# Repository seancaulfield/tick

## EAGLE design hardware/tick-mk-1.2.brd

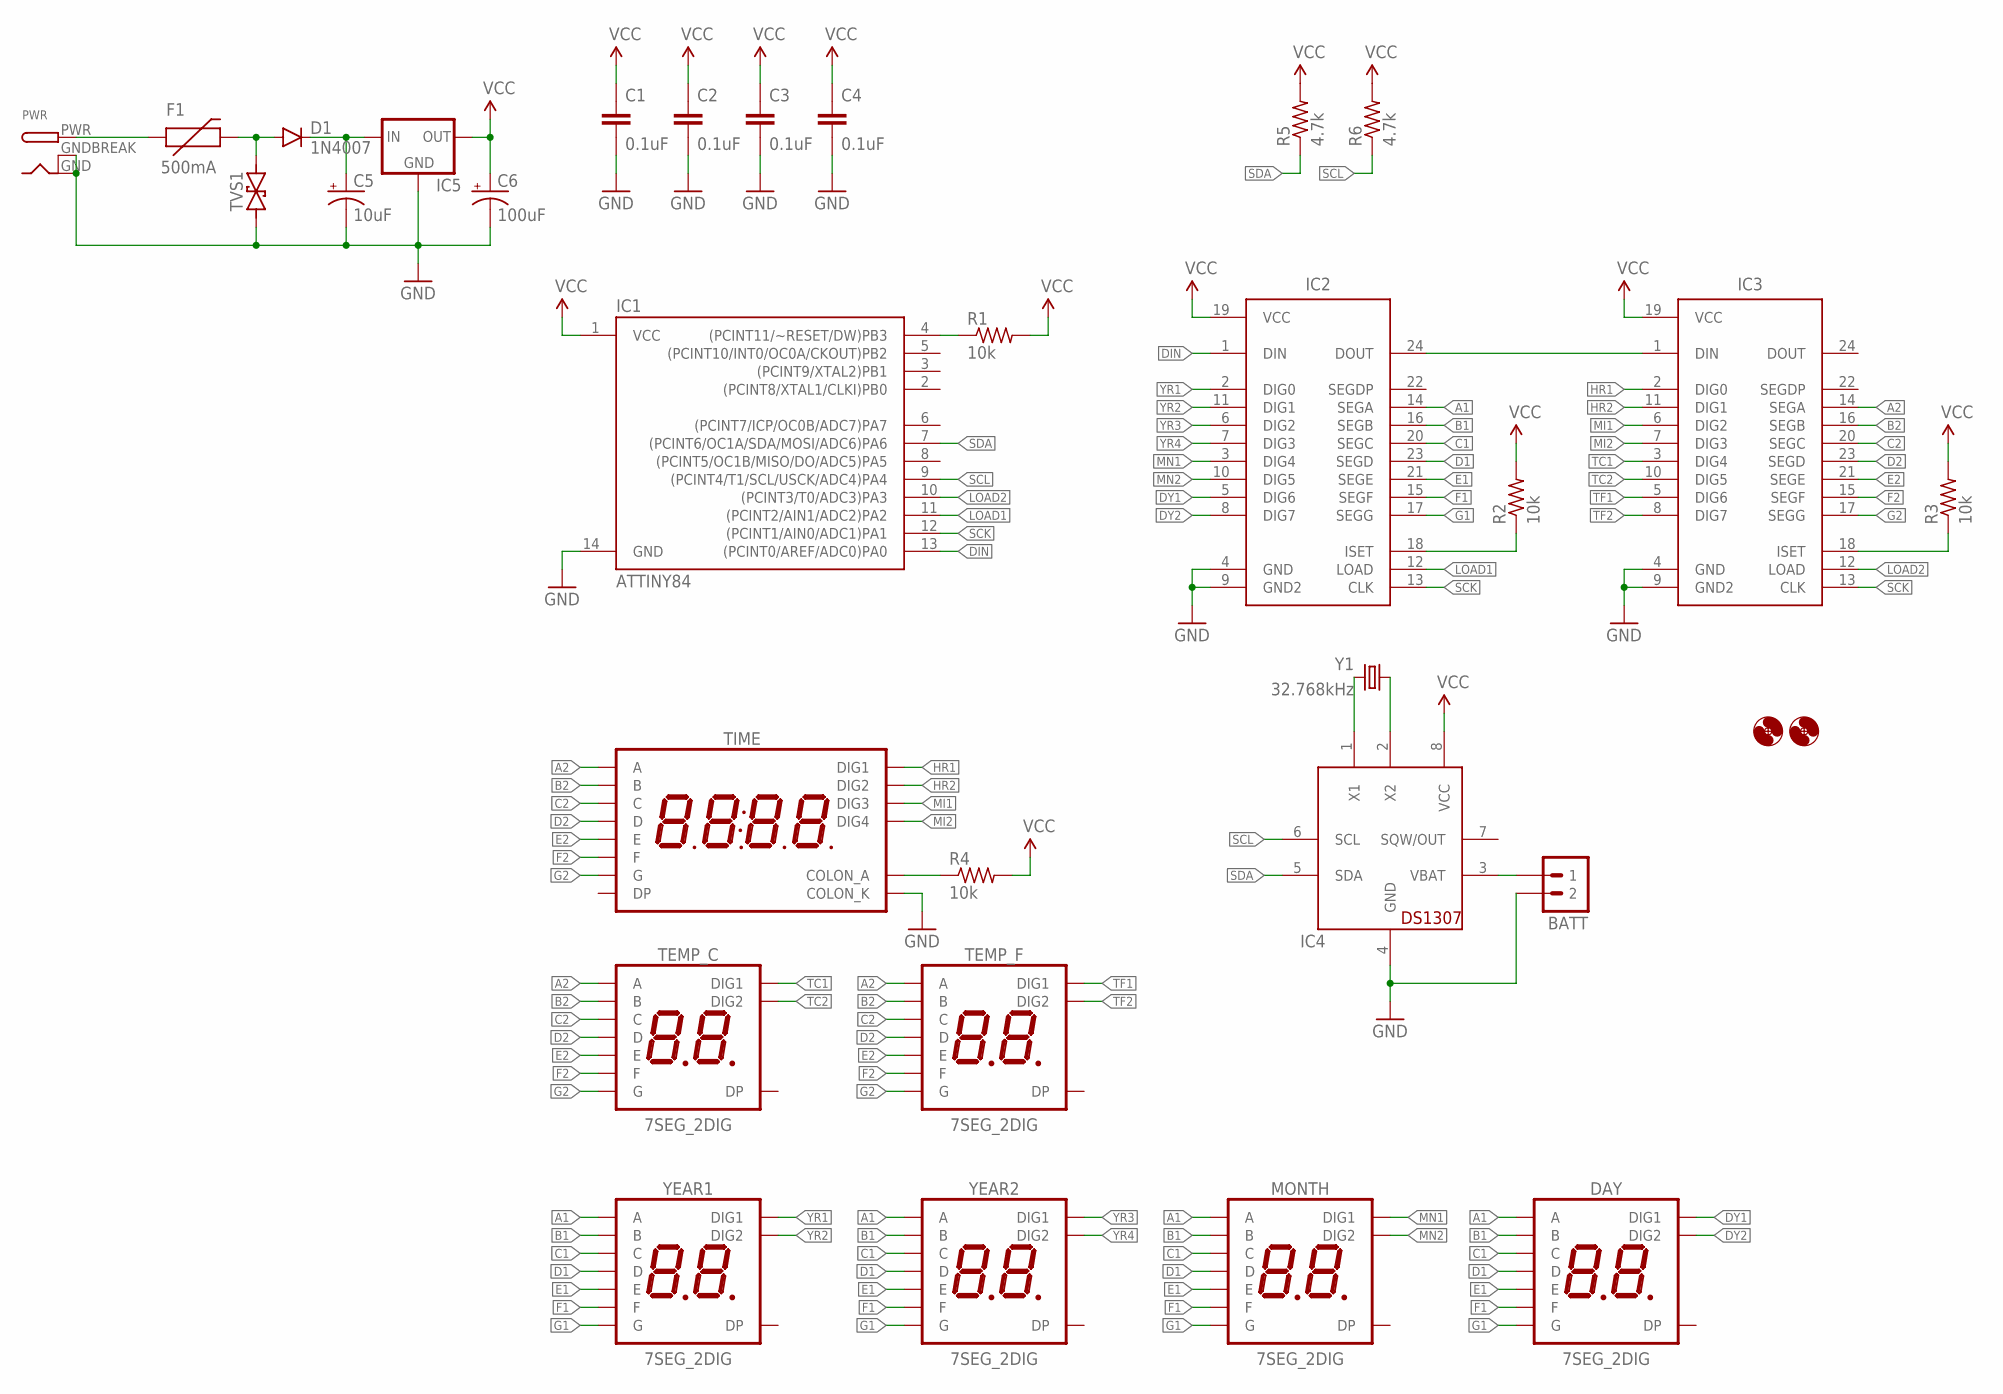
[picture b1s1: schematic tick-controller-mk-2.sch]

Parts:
BATT: M02JST-PTH-VERT; JST-2-PH-VERT-PTH
C1, C2, C3, C4: 0.1uF; C025-024X044
C5: 10uF; E2-5
C6: 100uF; E2-5
D1: 1N4007; DIODE-10.16MM
DAY: 7SEG_2DIG; 7SEG_2DIG_14MM
F1: 500mA; PTC
H1, H2: HOLE#2; HOLE-#2
IC1: ATTINY84; DIL14
IC2, IC3: MAX7219; DIL24
IC4: DS1307; DIL08
IC5: L7805; 78XXL
MONTH: 7SEG_2DIG; 7SEG_2DIG_14MM
PWR: DCBARRELPTH; DCJACK_2MM_PTH
R1, R2, R3, R4: 10k; RESISTOR-AXIAL-PTH-5.08MM
R5, R6: 4.7k; RESISTOR-AXIAL-PTH-5.08MM
TEMP_C: 7SEG_2DIG; 7SEG_2DIG_14MM
TEMP_F: 7SEG_2DIG; 7SEG_2DIG_14MM
TIME: 7SED_4DIGIT_14MM14.2MM-CC; 7SEG_4DIG
TVS1: TVSDO-41-TVS-BIDIRECTIONAL; DO-41-TVS
Y1: 32.768kHz; TC26H
YEAR1, YEAR2: 7SEG_2DIG; 7SEG_2DIG_14MM

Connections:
A1: DAY.4 (A), IC2.14 (SEGA), MONTH.4 (A), YEAR1.4 (A), YEAR2.4 (A)
A2: IC3.14 (SEGA), TEMP_C.4 (A), TEMP_F.4 (A), TIME.P$13 (A)
B1: DAY.3 (B), IC2.16 (SEGB), MONTH.3 (B), YEAR1.3 (B), YEAR2.3 (B)
B2: IC3.16 (SEGB), TEMP_C.3 (B), TEMP_F.3 (B), TIME.P$9 (B)
C1: DAY.9 (C), IC2.20 (SEGC), MONTH.9 (C), YEAR1.9 (C), YEAR2.9 (C)
C2: IC3.20 (SEGC), TEMP_C.9 (C), TEMP_F.9 (C), TIME.P$4 (C)
D1: DAY.8 (D), IC2.23 (SEGD), MONTH.8 (D), YEAR1.8 (D), YEAR2.8 (D)
D2: IC3.23 (SEGD), TEMP_C.8 (D), TEMP_F.8 (D), TIME.P$2 (D)
DIN: IC1.13 ((PCINT0/AREF/ADC0)PA0), IC2.1 (DIN)
DY1: DAY.5 (DIG1), IC2.5 (DIG6)
DY2: DAY.10 (DIG2), IC2.8 (DIG7)
E1: DAY.6 (E), IC2.21 (SEGE), MONTH.6 (E), YEAR1.6 (E), YEAR2.6 (E)
E2: IC3.21 (SEGE), TEMP_C.6 (E), TEMP_F.6 (E), TIME.P$1 (E)
F1: DAY.7 (F), IC2.15 (SEGF), MONTH.7 (F), YEAR1.7 (F), YEAR2.7 (F)
F2: IC3.15 (SEGF), TEMP_C.7 (F), TEMP_F.7 (F), TIME.P$12 (F)
G1: DAY.1 (G), IC2.17 (SEGG), MONTH.1 (G), YEAR1.1 (G), YEAR2.1 (G)
G2: IC3.17 (SEGG), TEMP_C.1 (G), TEMP_F.1 (G), TIME.P$5 (G)
GND: BATT.2, C1.2, C2.2, C3.2, C4.2, C5.-, C6.-, IC1.14 (GND), IC2.4 (GND), IC2.9 (GND2), IC3.4 (GND), IC3.9 (GND2), IC4.4 (GND), IC5.GND, PWR.GND, PWR.GNDBREAK, TIME.P$7 (COLON_K), TVS1.P$1 (1); also elsewhere on the board
HR1: IC3.2 (DIG0), TIME.P$14 (DIG1)
HR2: IC3.11 (DIG1), TIME.P$11 (DIG2)
LOAD1: IC1.11 ((PCINT2/AIN1/ADC2)PA2), IC2.12 (LOAD)
LOAD2: IC1.10 ((PCINT3/T0/ADC3)PA3), IC3.12 (LOAD)
MI1: IC3.6 (DIG2), TIME.P$10 (DIG3)
MI2: IC3.7 (DIG3), TIME.P$6 (DIG4)
MN1: IC2.3 (DIG4), MONTH.5 (DIG1)
MN2: IC2.10 (DIG5), MONTH.10 (DIG2)
unnamed: IC1.4 ((PCINT11/~RESET/DW)PB3), R1.P$1 (1)
unnamed: IC2.18 (ISET), R2.P$1 (1)
unnamed: IC4.1 (X1), Y1.2
unnamed 29: BATT.1, IC4.3 (VBAT); also elsewhere on the board
unnamed: IC4.2 (X2), Y1.1
unnamed 31: C5.+, D1.C, IC5.IN; also elsewhere on the board
unnamed: F1.P$1 (1), PWR.PWR
unnamed: D1.A, F1.P$2 (2), TVS1.P$2 (2)
unnamed: IC2.24 (DOUT), IC3.1 (DIN)
unnamed: IC3.18 (ISET), R3.P$1 (1)
unnamed: R4.P$1 (1), TIME.P$8 (COLON_A)
SCK: IC1.12 ((PCINT1/AIN0/ADC1)PA1), IC2.13 (CLK), IC3.13 (CLK)
SCL: IC1.9 ((PCINT4/T1/SCL/USCK/ADC4)PA4), IC4.6 (SCL), R6.P$1 (1)
SDA: IC1.7 ((PCINT6/OC1A/SDA/MOSI/ADC6)PA6), IC4.5 (SDA), R5.P$1 (1)
TC1: IC3.3 (DIG4), TEMP_C.5 (DIG1)
TC2: IC3.10 (DIG5), TEMP_C.10 (DIG2)
TF1: IC3.5 (DIG6), TEMP_F.5 (DIG1)
TF2: IC3.8 (DIG7), TEMP_F.10 (DIG2)
VCC: C1.1, C2.1, C3.1, C4.1, C6.+, IC1.1 (VCC), IC2.19 (VCC), IC3.19 (VCC), IC4.8 (VCC), IC5.OUT, R1.P$2 (2), R2.P$2 (2), R3.P$2 (2), R4.P$2 (2), R5.P$2 (2), R6.P$2 (2); also elsewhere on the board
YR1: IC2.2 (DIG0), YEAR1.5 (DIG1)
YR2: IC2.11 (DIG1), YEAR1.10 (DIG2)
YR3: IC2.6 (DIG2), YEAR2.5 (DIG1)
YR4: IC2.7 (DIG3), YEAR2.10 (DIG2)

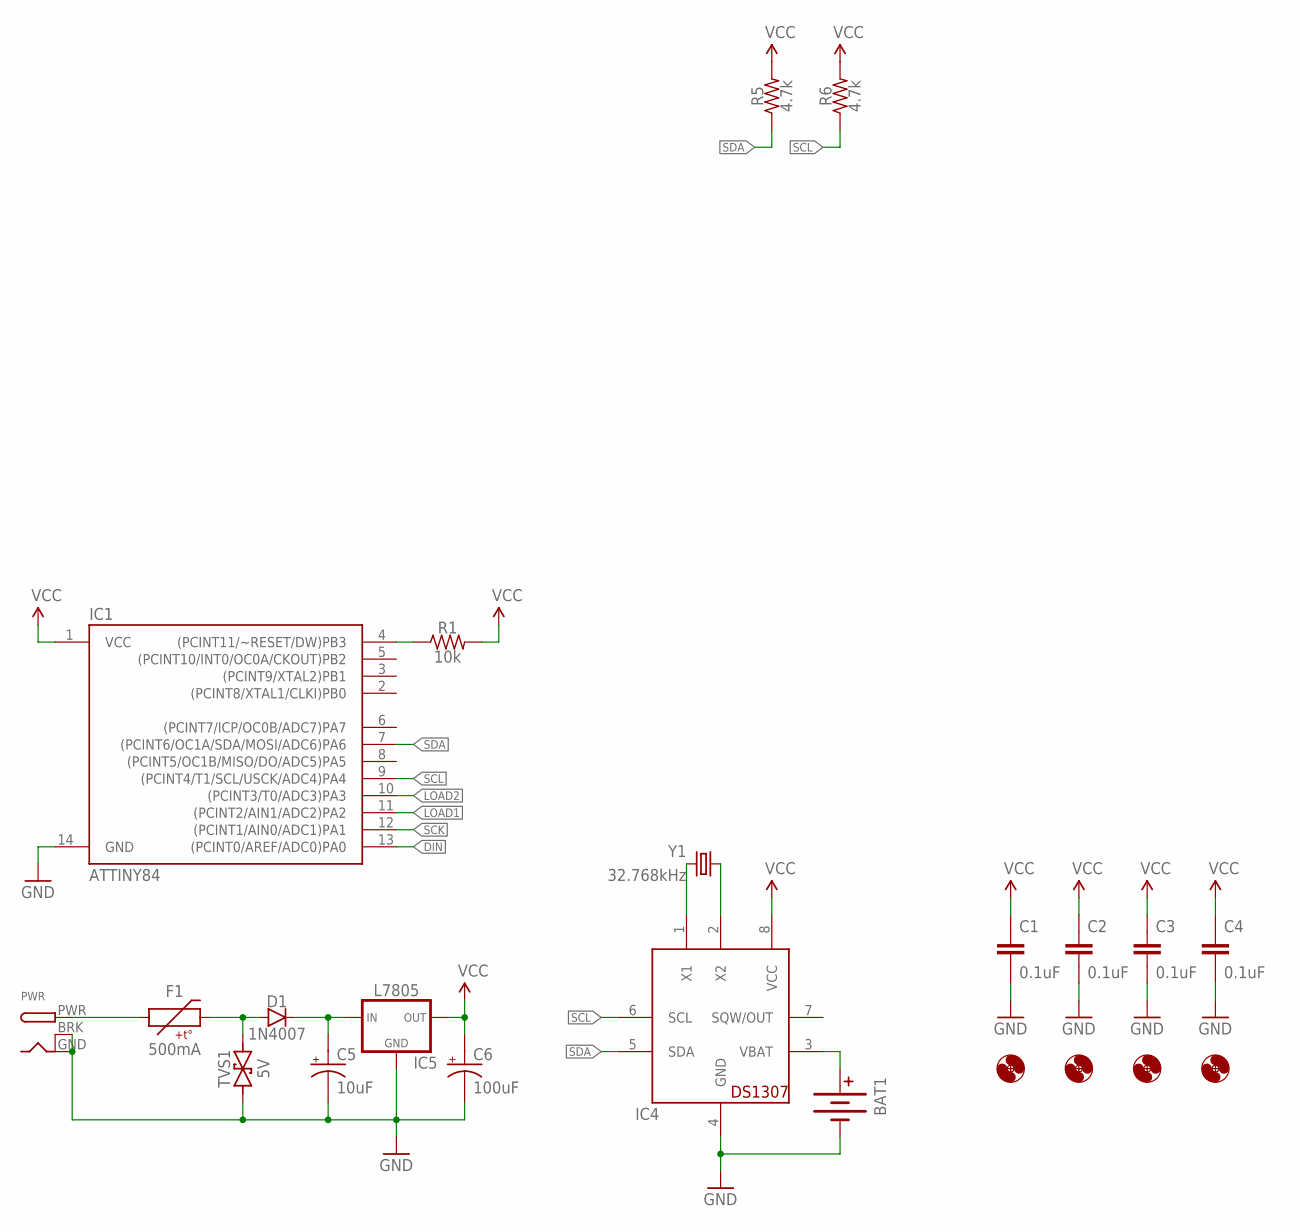
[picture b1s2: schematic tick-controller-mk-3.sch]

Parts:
BAT1: BATTERY20SMD; BATTCON_20MM
C1, C2, C3, C4: 0.1uF; C025-024X044
C5: 10uF; E2-5
C6: 100uF; E2-5
D1: 1N4007; DIODE-10.16MM
F1: 500mA; PTC-PTH-5.08MM
H1, H2, H3, H4: HOLE#2; HOLE-#2
IC1: ATTINY84; DIL14
IC4: DS1307; DIL08
IC5: L7805; TO-92-AMMO
PWR: DCBARRELPTH; DCJACK_2MM_PTH
R1: 10k; RESISTOR-AXIAL-PTH-5.08MM
R5, R6: 4.7k; RESISTOR-AXIAL-PTH-5.08MM
TVS1: 5V; DO-41-TVS-BI-10.16MM
Y1: 32.768kHz; TC26H

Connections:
DIN: IC1.13 ((PCINT0/AREF/ADC0)PA0); also elsewhere on the board
GND: BAT1.2 (-), C1.2, C2.2, C3.2, C4.2, C5.-, C6.-, IC1.14 (GND), IC4.4 (GND), IC5.2 (GND), PWR.BRK, PWR.GND, TVS1.P$1 (1); also elsewhere on the board
LOAD1: IC1.11 ((PCINT2/AIN1/ADC2)PA2); also elsewhere on the board
LOAD2: IC1.10 ((PCINT3/T0/ADC3)PA3); also elsewhere on the board
unnamed: IC1.4 ((PCINT11/~RESET/DW)PB3), R1.P$1 (1)
unnamed: IC4.1 (X1), Y1.2
unnamed 29: BAT1.1 (+), IC4.3 (VBAT); also elsewhere on the board
unnamed: IC4.2 (X2), Y1.1
unnamed 31: C5.+, D1.C, IC5.1 (IN); also elsewhere on the board
unnamed: F1.P$1 (1), PWR.PWR
unnamed: D1.A, F1.P$2 (2), TVS1.P$2 (2)
SCK: IC1.12 ((PCINT1/AIN0/ADC1)PA1); also elsewhere on the board
SCL: IC1.9 ((PCINT4/T1/SCL/USCK/ADC4)PA4), IC4.6 (SCL), R6.P$1 (1)
SDA: IC1.7 ((PCINT6/OC1A/SDA/MOSI/ADC6)PA6), IC4.5 (SDA), R5.P$1 (1)
VCC: C1.1, C2.1, C3.1, C4.1, C6.+, IC1.1 (VCC), IC4.8 (VCC), IC5.3 (OUT), R1.P$2 (2), R5.P$2 (2), R6.P$2 (2); also elsewhere on the board

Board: 2 copper layers, 32 parts (13 on the bottom side), 49 nets, no tracks yet.

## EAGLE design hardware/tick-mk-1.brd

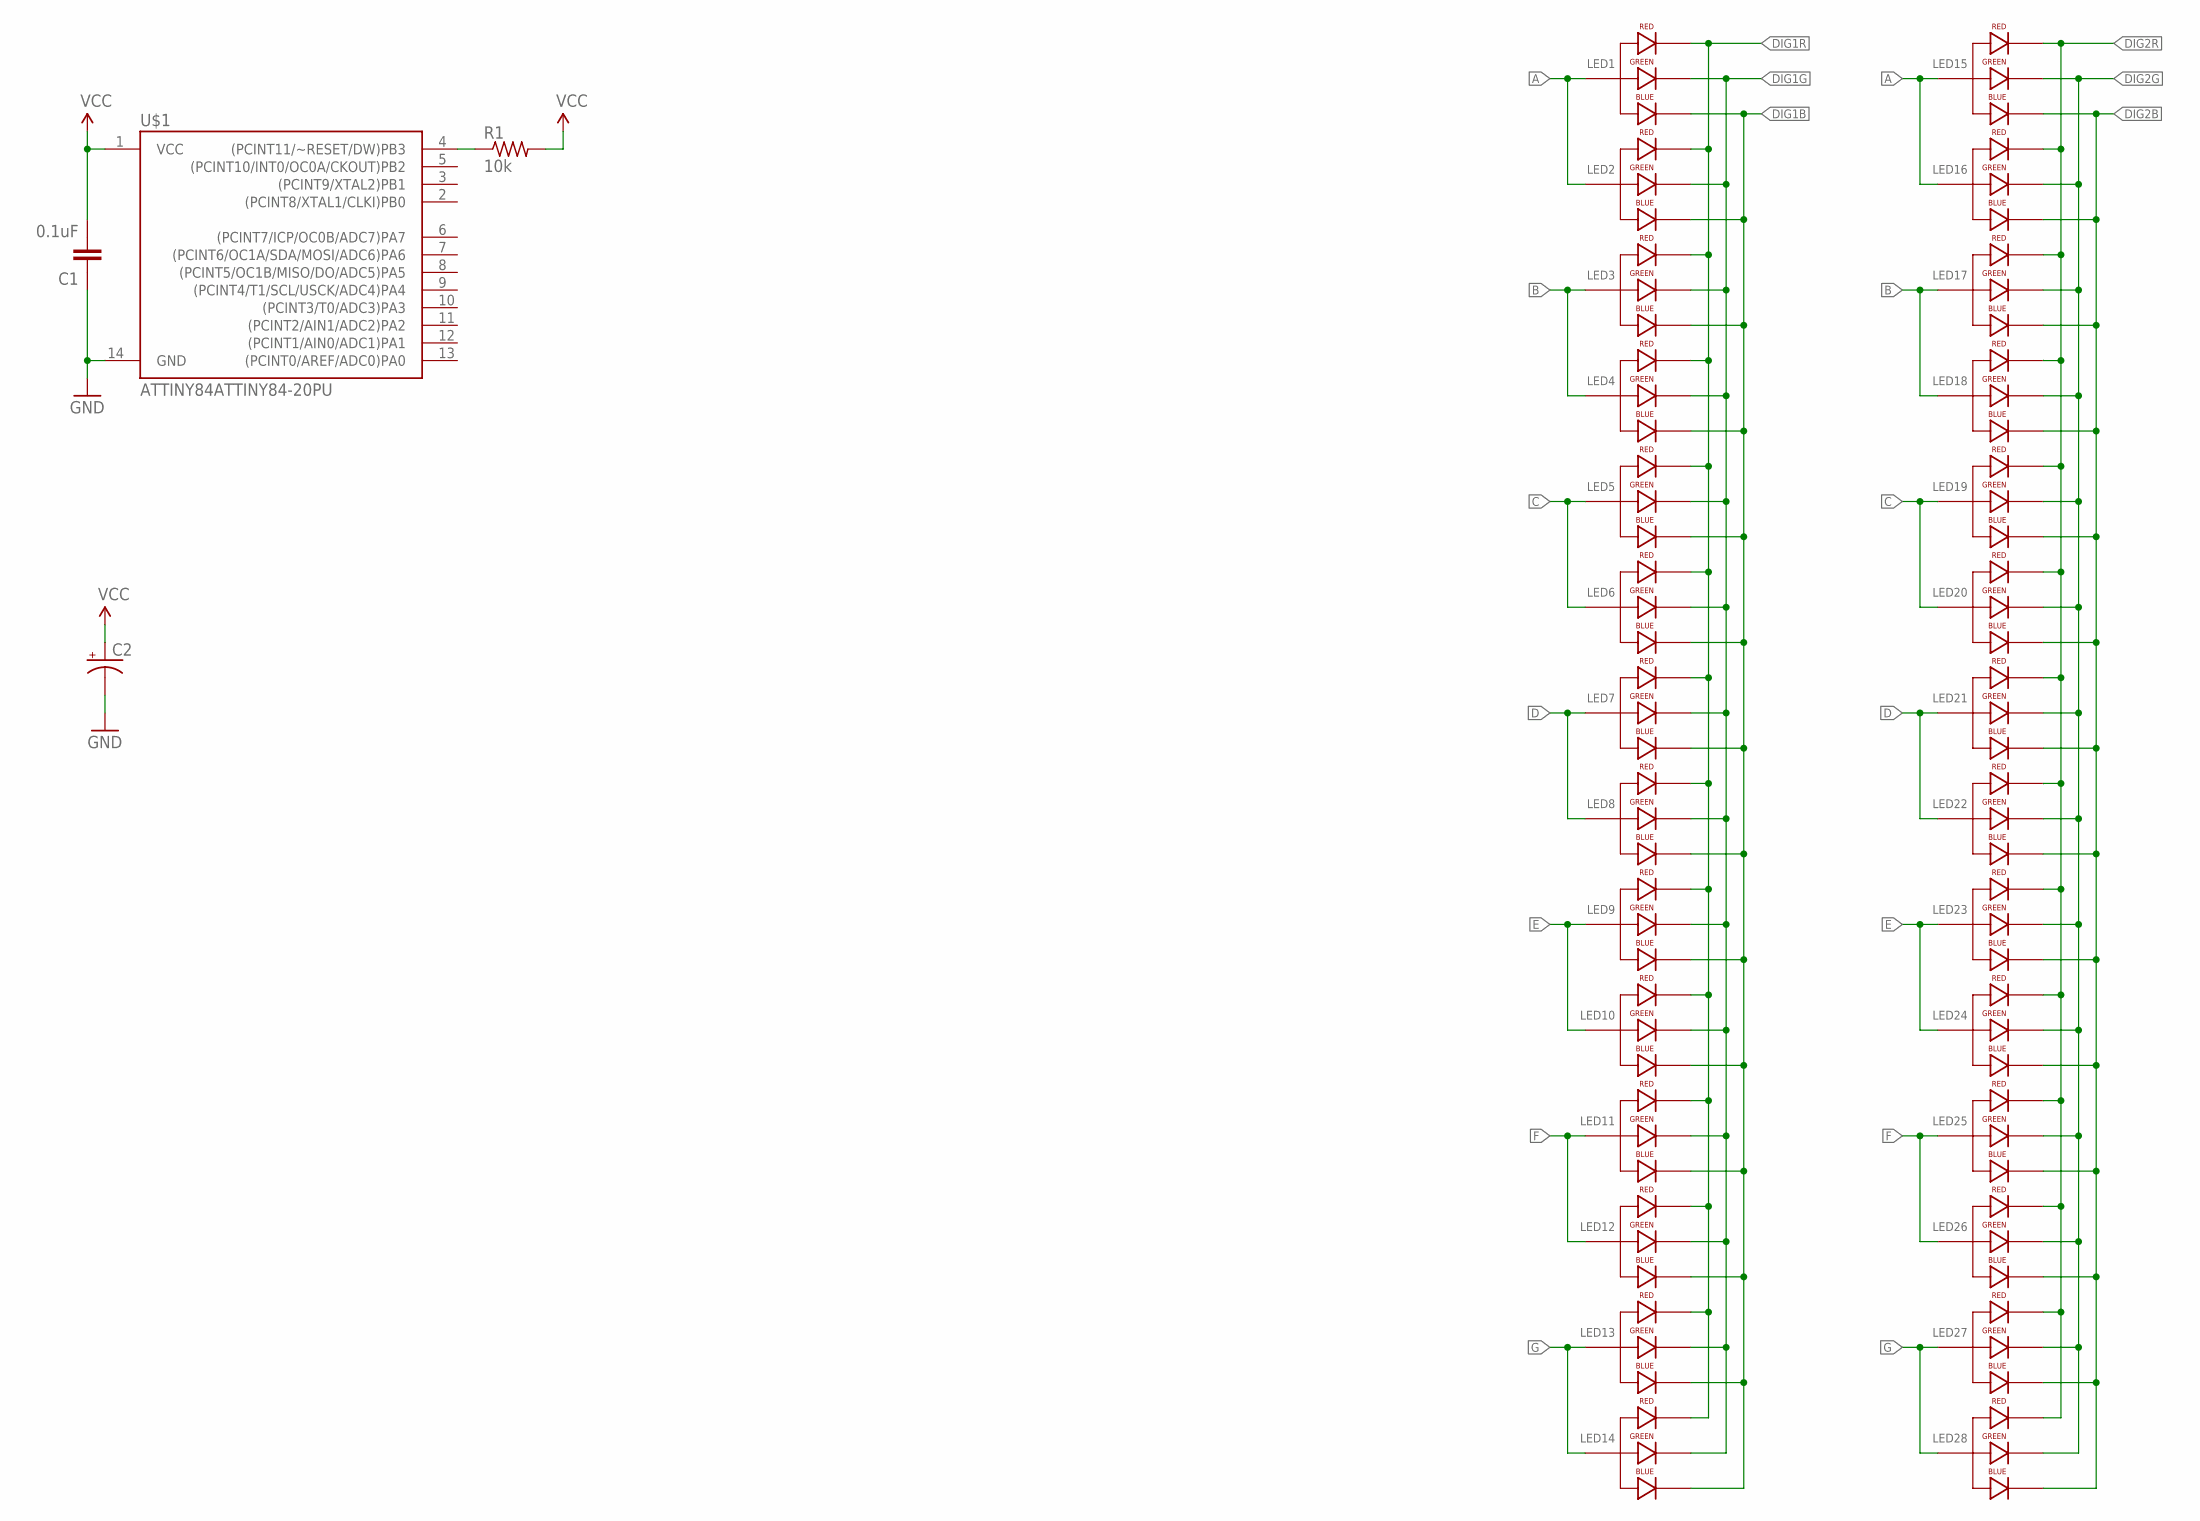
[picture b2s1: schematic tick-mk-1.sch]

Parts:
C1: 0.1uF; C025-024X044
C2: CAPACITOR-POLARIZEDE2-5; E2-5
LED1, LED2, LED3, LED4, LED5, LED6, LED7, LED8, LED9, LED10, LED11, LED12, LED13, LED14, LED15, LED16, LED17, LED18, LED19, LED20, LED21, LED22, LED23, LED24, LED25, LED26, LED27, LED28: LED-RGB-CA-THRUCLEAR; LED-RGB-THRU
R1: 10k; RESISTOR-AXIAL-PTH-5.08MM
U$1: ATTINY84ATTINY84-20PU; DIL14

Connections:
A: LED1.2 (ANODE), LED2.2 (ANODE), LED15.2 (ANODE), LED16.2 (ANODE)
B: LED3.2 (ANODE), LED4.2 (ANODE), LED17.2 (ANODE), LED18.2 (ANODE)
C: LED5.2 (ANODE), LED6.2 (ANODE), LED19.2 (ANODE), LED20.2 (ANODE)
D: LED7.2 (ANODE), LED8.2 (ANODE), LED21.2 (ANODE), LED22.2 (ANODE)
DIG1B: LED1.4 (BLUE_CATHODE), LED2.4 (BLUE_CATHODE), LED3.4 (BLUE_CATHODE), LED4.4 (BLUE_CATHODE), LED5.4 (BLUE_CATHODE), LED6.4 (BLUE_CATHODE), LED7.4 (BLUE_CATHODE), LED8.4 (BLUE_CATHODE), LED9.4 (BLUE_CATHODE), LED10.4 (BLUE_CATHODE), LED11.4 (BLUE_CATHODE), LED12.4 (BLUE_CATHODE), LED13.4 (BLUE_CATHODE), LED14.4 (BLUE_CATHODE)
DIG1G: LED1.3 (GREEN_CATHODE), LED2.3 (GREEN_CATHODE), LED3.3 (GREEN_CATHODE), LED4.3 (GREEN_CATHODE), LED5.3 (GREEN_CATHODE), LED6.3 (GREEN_CATHODE), LED7.3 (GREEN_CATHODE), LED8.3 (GREEN_CATHODE), LED9.3 (GREEN_CATHODE), LED10.3 (GREEN_CATHODE), LED11.3 (GREEN_CATHODE), LED12.3 (GREEN_CATHODE), LED13.3 (GREEN_CATHODE), LED14.3 (GREEN_CATHODE)
DIG1R: LED1.1 (RED_CATHODE), LED2.1 (RED_CATHODE), LED3.1 (RED_CATHODE), LED4.1 (RED_CATHODE), LED5.1 (RED_CATHODE), LED6.1 (RED_CATHODE), LED7.1 (RED_CATHODE), LED8.1 (RED_CATHODE), LED9.1 (RED_CATHODE), LED10.1 (RED_CATHODE), LED11.1 (RED_CATHODE), LED12.1 (RED_CATHODE), LED13.1 (RED_CATHODE), LED14.1 (RED_CATHODE)
DIG2B: LED15.4 (BLUE_CATHODE), LED16.4 (BLUE_CATHODE), LED17.4 (BLUE_CATHODE), LED18.4 (BLUE_CATHODE), LED19.4 (BLUE_CATHODE), LED20.4 (BLUE_CATHODE), LED21.4 (BLUE_CATHODE), LED22.4 (BLUE_CATHODE), LED23.4 (BLUE_CATHODE), LED24.4 (BLUE_CATHODE), LED25.4 (BLUE_CATHODE), LED26.4 (BLUE_CATHODE), LED27.4 (BLUE_CATHODE), LED28.4 (BLUE_CATHODE)
DIG2G: LED15.3 (GREEN_CATHODE), LED16.3 (GREEN_CATHODE), LED17.3 (GREEN_CATHODE), LED18.3 (GREEN_CATHODE), LED19.3 (GREEN_CATHODE), LED20.3 (GREEN_CATHODE), LED21.3 (GREEN_CATHODE), LED22.3 (GREEN_CATHODE), LED23.3 (GREEN_CATHODE), LED24.3 (GREEN_CATHODE), LED25.3 (GREEN_CATHODE), LED26.3 (GREEN_CATHODE), LED27.3 (GREEN_CATHODE), LED28.3 (GREEN_CATHODE)
DIG2R: LED15.1 (RED_CATHODE), LED16.1 (RED_CATHODE), LED17.1 (RED_CATHODE), LED18.1 (RED_CATHODE), LED19.1 (RED_CATHODE), LED20.1 (RED_CATHODE), LED21.1 (RED_CATHODE), LED22.1 (RED_CATHODE), LED23.1 (RED_CATHODE), LED24.1 (RED_CATHODE), LED25.1 (RED_CATHODE), LED26.1 (RED_CATHODE), LED27.1 (RED_CATHODE), LED28.1 (RED_CATHODE)
E: LED9.2 (ANODE), LED10.2 (ANODE), LED23.2 (ANODE), LED24.2 (ANODE)
F: LED11.2 (ANODE), LED12.2 (ANODE), LED25.2 (ANODE), LED26.2 (ANODE)
G: LED13.2 (ANODE), LED14.2 (ANODE), LED27.2 (ANODE), LED28.2 (ANODE)
GND: C1.1, C2.-, U$1.14 (GND)
unnamed: R1.P$1 (1), U$1.4 ((PCINT11/~RESET/DW)PB3)
VCC: C1.2, C2.+, R1.P$2 (2), U$1.1 (VCC)

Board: 2 copper layers, 32 parts (0 on the bottom side), 16 nets, no tracks yet.

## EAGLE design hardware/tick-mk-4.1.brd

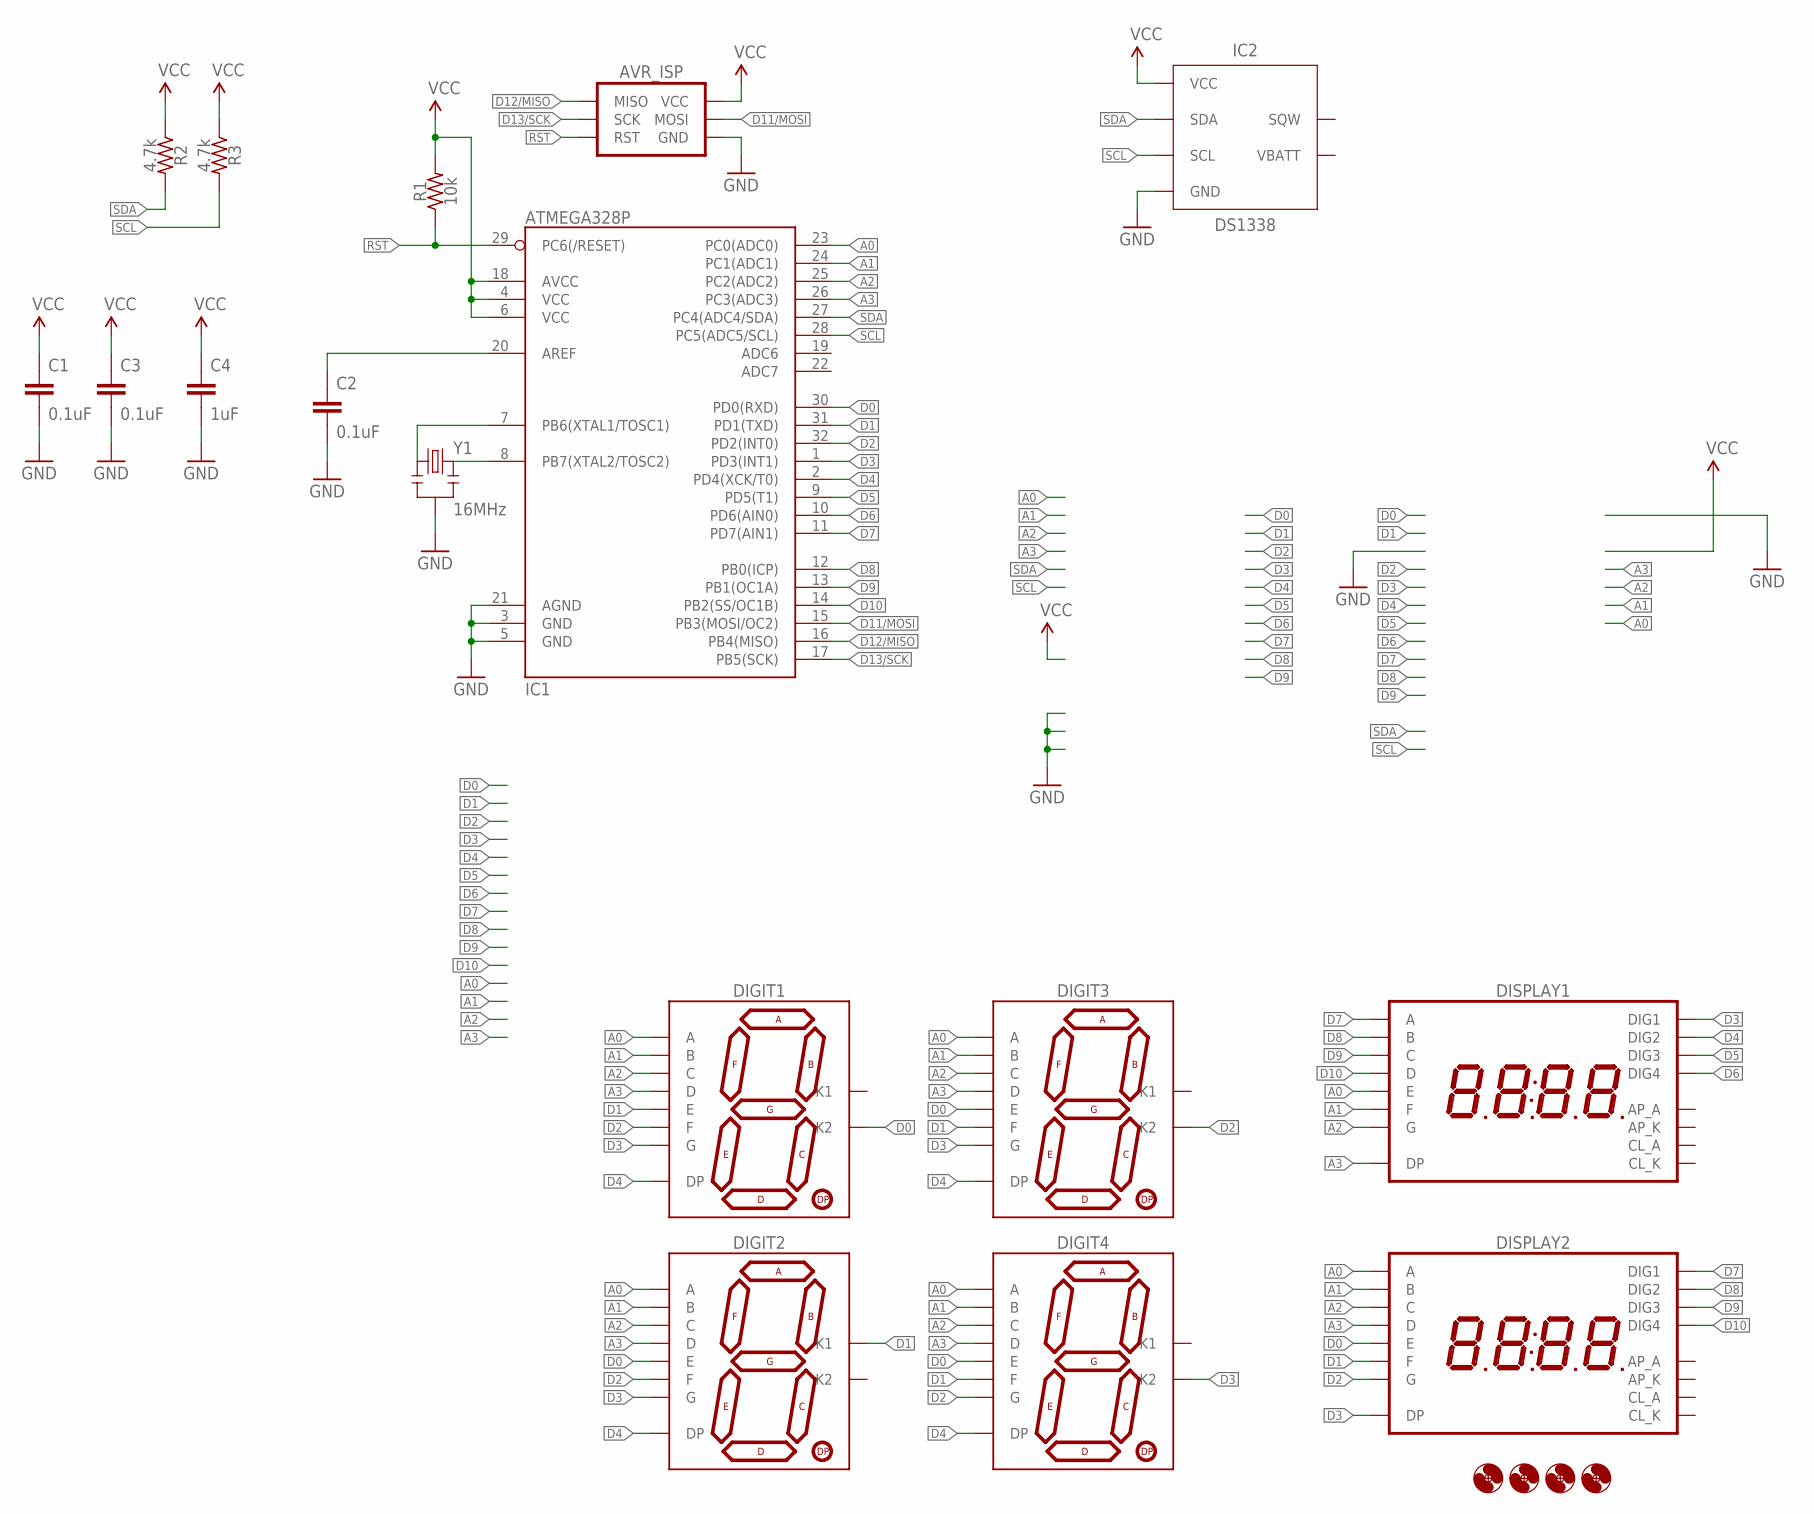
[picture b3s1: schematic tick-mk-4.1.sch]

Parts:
AVR_ISP: AVR_SPI_PRG_6PTH; 2X3
C1, C2, C3: 0.1uF; C0805
C4: 1uF; C0805
DIGIT1, DIGIT2, DIGIT3, DIGIT4: 7SEG_1DIGPTH-25.4MM; 7SEG_1DIG_25.4MM
DISPLAY1, DISPLAY2: 7SEG_4DIGIT_COLON_APOS; 7SEG_4DIG_10MM
H1, H2, H3, H4: HOLE#2; HOLE-#2
IC1: ATMEGA328P; TQFP32-08
IC2: DS1338; SO16W
R1: 10k; R0805
R2, R3: 4.7k; R0805
Y1: 16MHz; RESONATOR-4.7X4.1X1.2MM

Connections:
A0: DIGIT1.7 (A), DIGIT2.7 (A), DIGIT3.7 (A), DIGIT4.7 (A), DISPLAY1.5 (E), DISPLAY2.14 (A), IC1.23 (PC0(ADC0))
A1: DIGIT1.6 (B), DIGIT2.6 (B), DIGIT3.6 (B), DIGIT4.6 (B), DISPLAY1.11 (F), DISPLAY2.16 (B), IC1.24 (PC1(ADC1))
A2: DIGIT1.4 (C), DIGIT2.4 (C), DIGIT3.4 (C), DIGIT4.4 (C), DISPLAY1.15 (G), DISPLAY2.13 (C), IC1.25 (PC2(ADC2))
A3: DIGIT1.2 (D), DIGIT2.2 (D), DIGIT3.2 (D), DIGIT4.2 (D), DISPLAY1.7 (DP), DISPLAY2.3 (D), IC1.26 (PC3(ADC3))
D0: DIGIT1.8 (K2), DIGIT2.1 (E), DIGIT3.1 (E), DIGIT4.1 (E), DISPLAY2.5 (E), IC1.30 (PD0(RXD))
D1: DIGIT1.1 (E), DIGIT2.3 (K1), DIGIT3.9 (F), DIGIT4.9 (F), DISPLAY2.11 (F), IC1.31 (PD1(TXD))
D2: DIGIT1.9 (F), DIGIT2.9 (F), DIGIT3.8 (K2), DIGIT4.10 (G), DISPLAY2.15 (G), IC1.32 (PD2(INT0))
D3: DIGIT1.10 (G), DIGIT2.10 (G), DIGIT3.10 (G), DIGIT4.8 (K2), DISPLAY1.1 (DIG1), DISPLAY2.7 (DP), IC1.1 (PD3(INT1))
D4: DIGIT1.5 (DP), DIGIT2.5 (DP), DIGIT3.5 (DP), DIGIT4.5 (DP), DISPLAY1.2 (DIG2), IC1.2 (PD4(XCK/T0))
D5: DISPLAY1.6 (DIG3), IC1.9 (PD5(T1))
D6: DISPLAY1.8 (DIG4), IC1.10 (PD6(AIN0))
D7: DISPLAY1.14 (A), DISPLAY2.1 (DIG1), IC1.11 (PD7(AIN1))
D8: DISPLAY1.16 (B), DISPLAY2.2 (DIG2), IC1.12 (PB0(ICP))
D9: DISPLAY1.13 (C), DISPLAY2.6 (DIG3), IC1.13 (PB1(OC1A))
D10: DISPLAY1.3 (D), DISPLAY2.8 (DIG4), IC1.14 (PB2(SS/OC1B))
D11/MOSI: AVR_ISP.4 (MOSI), IC1.15 (PB3(MOSI/OC2))
D12/MISO: AVR_ISP.1 (MISO), IC1.16 (PB4(MISO))
D13/SCK: AVR_ISP.3 (SCK), IC1.17 (PB5(SCK))
GND: AVR_ISP.6 (GND), C1.2, C2.2, C3.2, C4.2, IC1.3 (GND), IC1.5 (GND), IC1.21 (AGND), IC2.4 (GND), IC2.5 (GND), IC2.6 (GND), IC2.7 (GND), IC2.8 (GND), IC2.9 (GND), IC2.10 (GND), IC2.11 (GND), IC2.12 (GND), IC2.13 (GND), IC2.15 (GND), Y1.2
unnamed: C2.1, IC1.20 (AREF)
unnamed: IC1.7 (PB6(XTAL1/TOSC1)), Y1.1
unnamed: IC1.8 (PB7(XTAL2/TOSC2)), Y1.3
RST: AVR_ISP.5 (RST), IC1.29 (PC6(/RESET)), R1.1
SCL: IC1.28 (PC5(ADC5/SCL)), IC2.1 (SCL), R3.2
SDA: IC1.27 (PC4(ADC4/SDA)), IC2.16 (SDA), R2.2
VCC: AVR_ISP.2 (VCC), C1.1, C3.1, C4.1, IC1.4 (VCC), IC1.6 (VCC), IC1.18 (AVCC), IC2.3 (VCC), R1.2, R2.1, R3.1

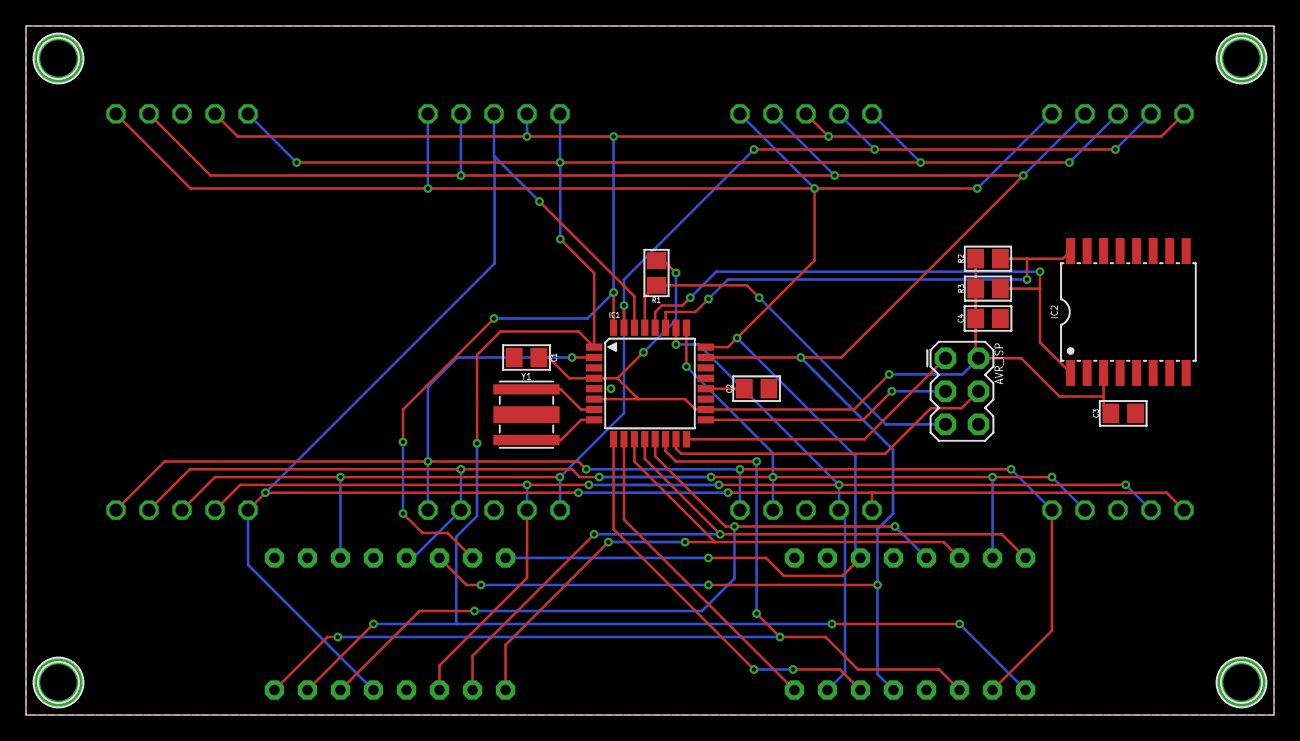
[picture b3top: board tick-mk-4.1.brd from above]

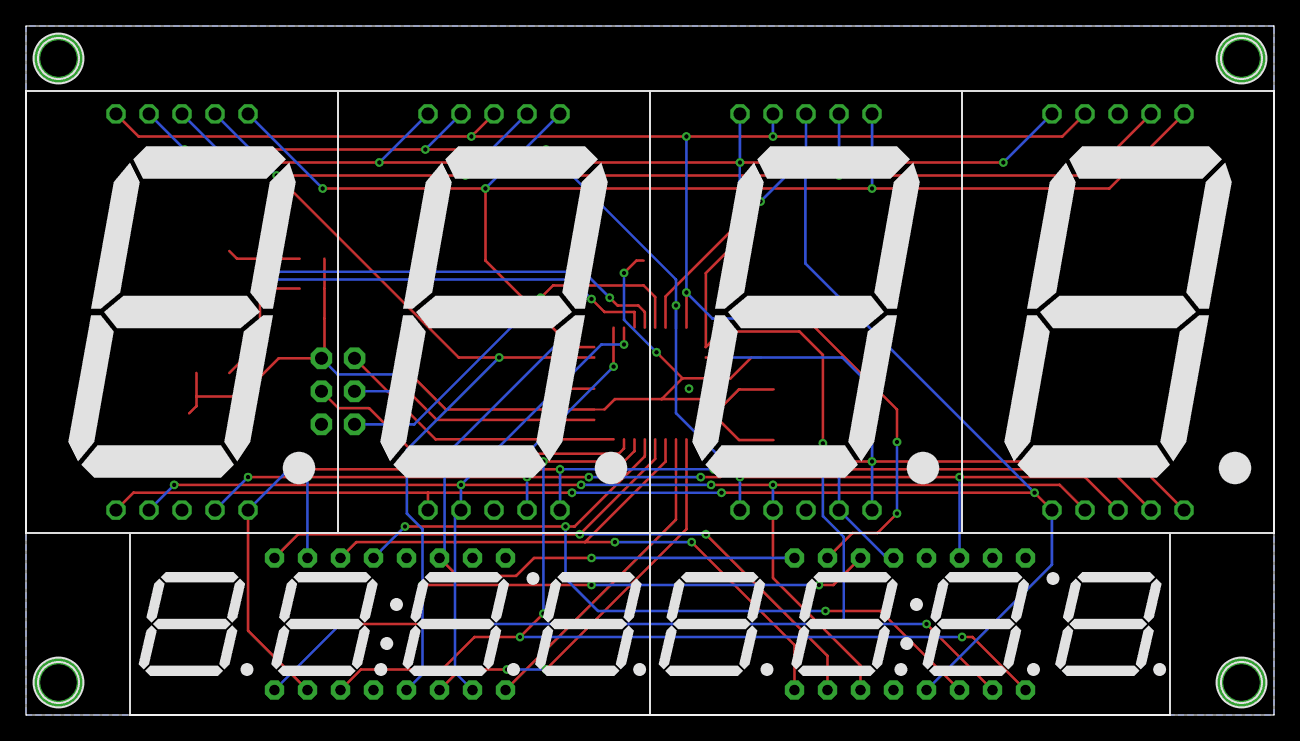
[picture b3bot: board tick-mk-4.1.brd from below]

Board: 2 copper layers, 96.0 x 53.0 mm, 21 parts (6 on the bottom side), 26 nets.
